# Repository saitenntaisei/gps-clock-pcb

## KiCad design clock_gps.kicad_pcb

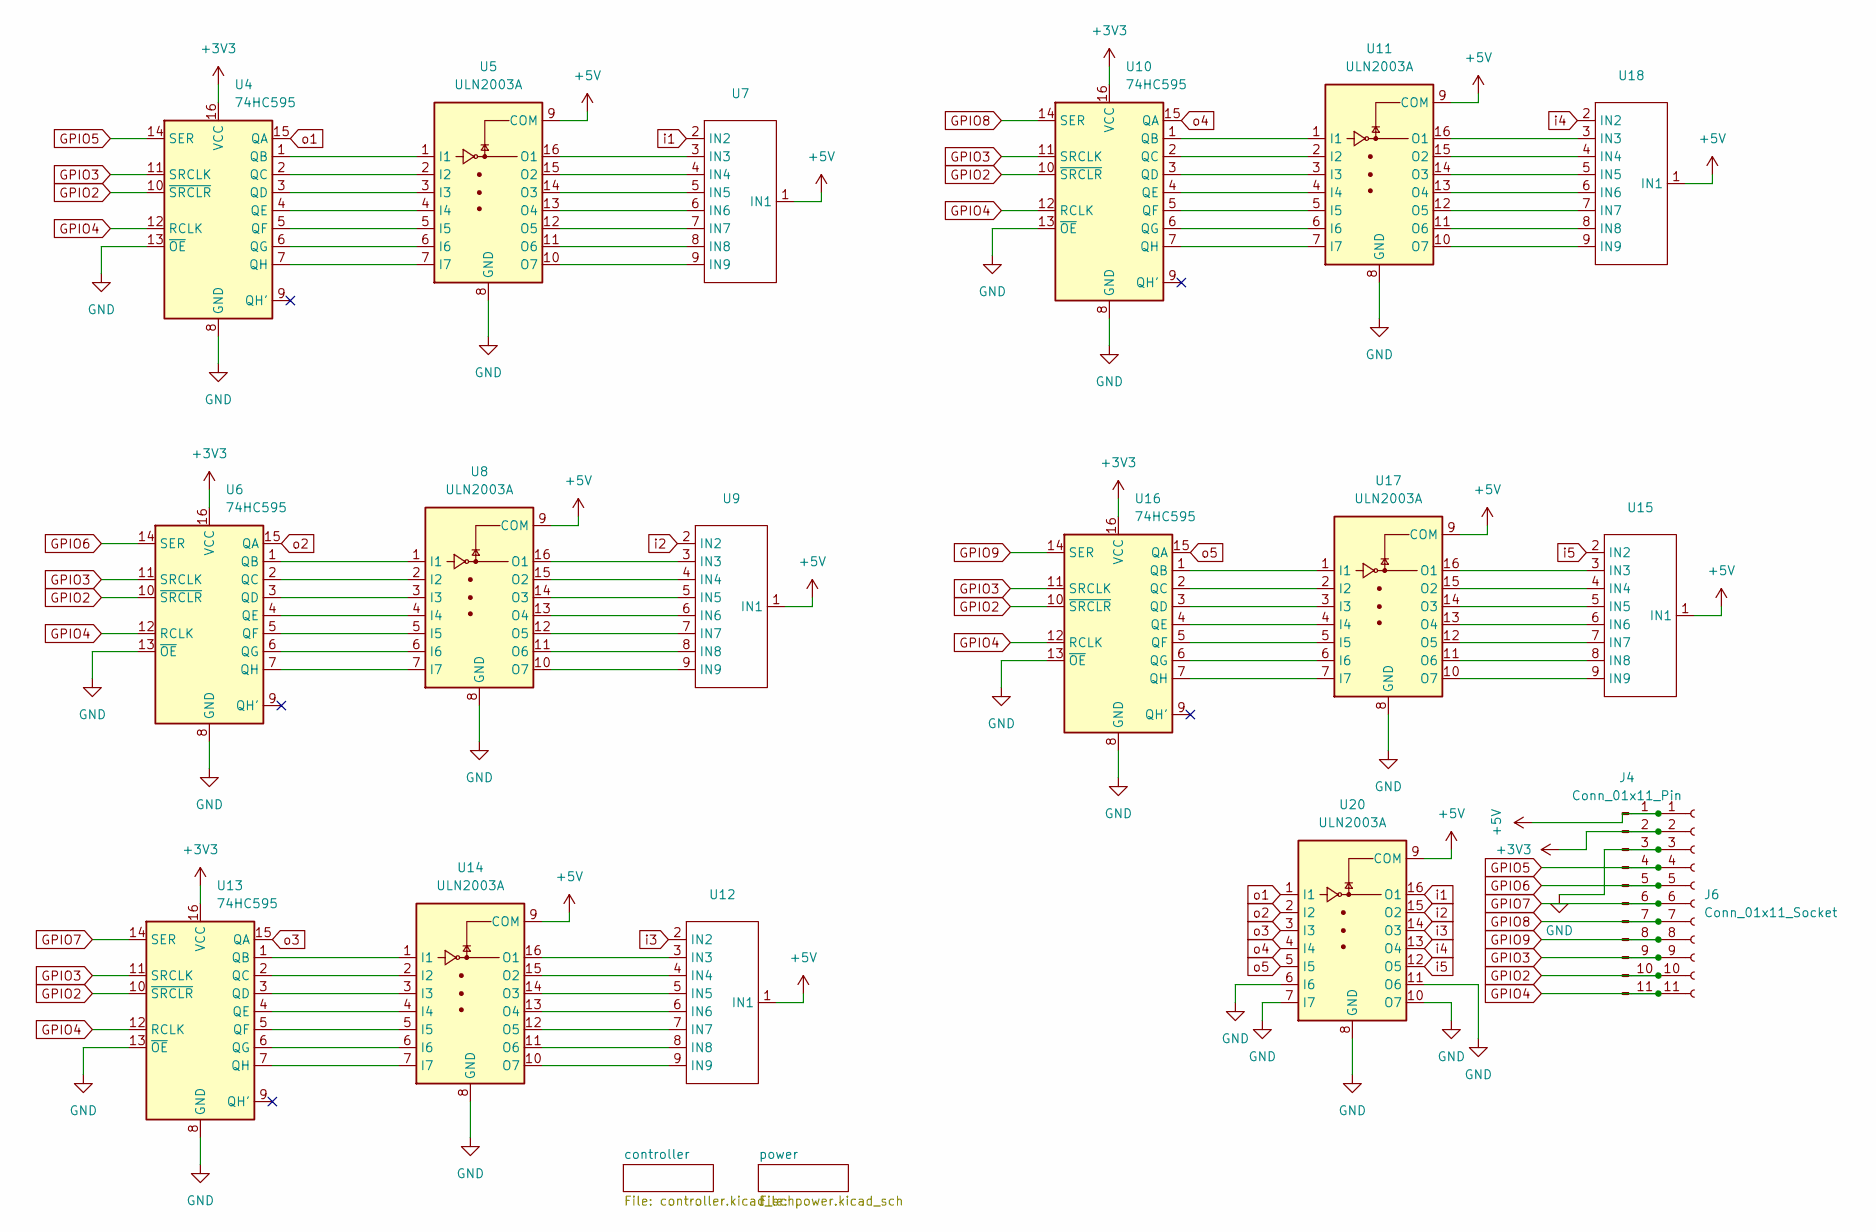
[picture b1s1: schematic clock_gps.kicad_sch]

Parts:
J4: Conn_01x11_Pin; PinHeader_1x11_P2.54mm_Vertical
J6: Conn_01x11_Socket; PinSocket_1x11_P2.54mm_Vertical
U4, U6, U10, U13, U16: 74HC595; SOIC-16_3.9x9.9mm_P1.27mm
U5, U8, U11, U14, U17, U20: ULN2003A; SOIC-16_3.9x9.9mm_P1.27mm
U7, U9, U12, U15, U18: NUM_IV-9

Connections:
+3V3: J4.2, J6.2, U4.16 (VCC), U6.16 (VCC), U10.16 (VCC), U13.16 (VCC), U16.16 (VCC); also elsewhere on the board
+5V: J4.1, J6.1, U5.9 (COM), U7.1 (IN1), U8.9 (COM), U9.1 (IN1), U11.9 (COM), U12.1 (IN1), U14.9 (COM), U15.1 (IN1), U17.9 (COM), U18.1 (IN1), U20.9 (COM); also elsewhere on the board
GND: J4.3, J6.3, U4.8 (GND), U4.13 (~OE), U5.8 (GND), U6.8 (GND), U6.13 (~OE), U8.8 (GND), U10.8 (GND), U10.13 (~OE), U11.8 (GND), U13.8 (GND), U13.13 (~OE), U14.8 (GND), U16.8 (GND), U16.13 (~OE), U17.8 (GND), U20.6 (I6), U20.7 (I7), U20.8 (GND), U20.10 (O7), U20.11 (O6); also elsewhere on the board
GPIO2: J4.10, J6.10, U4.10 (~SRCLR), U6.10 (~SRCLR), U10.10 (~SRCLR), U13.10 (~SRCLR), U16.10 (~SRCLR); also elsewhere on the board
GPIO3: J4.9, J6.9, U4.11 (SRCLK), U6.11 (SRCLK), U10.11 (SRCLK), U13.11 (SRCLK), U16.11 (SRCLK); also elsewhere on the board
GPIO4: J4.11, J6.11, U4.12 (RCLK), U6.12 (RCLK), U10.12 (RCLK), U13.12 (RCLK), U16.12 (RCLK); also elsewhere on the board
GPIO5: J4.4, J6.4, U4.14 (SER); also elsewhere on the board
GPIO6: J4.5, J6.5, U6.14 (SER); also elsewhere on the board
GPIO7: J4.6, J6.6, U13.14 (SER); also elsewhere on the board
GPIO8: J4.7, J6.7, U10.14 (SER); also elsewhere on the board
GPIO9: J4.8, J6.8, U16.14 (SER); also elsewhere on the board
unnamed: U4.1 (QB), U5.1 (I1)
unnamed: U4.2 (QC), U5.2 (I2)
unnamed: U4.3 (QD), U5.3 (I3)
unnamed: U4.4 (QE), U5.4 (I4)
unnamed: U4.5 (QF), U5.5 (I5)
unnamed: U4.6 (QG), U5.6 (I6)
unnamed: U4.7 (QH), U5.7 (I7)
unnamed: U5.16 (O1), U7.3 (IN3)
unnamed: U5.15 (O2), U7.4 (IN4)
unnamed: U5.14 (O3), U7.5 (IN5)
unnamed: U5.13 (O4), U7.6 (IN6)
unnamed: U5.12 (O5), U7.7 (IN7)
unnamed: U5.11 (O6), U7.8 (IN8)
unnamed: U5.10 (O7), U7.9 (IN9)
unnamed: U6.1 (QB), U8.1 (I1)
unnamed: U6.2 (QC), U8.2 (I2)
unnamed: U6.3 (QD), U8.3 (I3)
unnamed: U6.4 (QE), U8.4 (I4)
unnamed: U6.5 (QF), U8.5 (I5)
unnamed: U6.6 (QG), U8.6 (I6)
unnamed: U6.7 (QH), U8.7 (I7)
unnamed: U8.16 (O1), U9.3 (IN3)
unnamed: U8.15 (O2), U9.4 (IN4)
unnamed: U8.14 (O3), U9.5 (IN5)
unnamed: U8.13 (O4), U9.6 (IN6)
unnamed: U8.12 (O5), U9.7 (IN7)
unnamed: U8.11 (O6), U9.8 (IN8)
unnamed: U8.10 (O7), U9.9 (IN9)
unnamed: U10.1 (QB), U11.1 (I1)
unnamed: U10.2 (QC), U11.2 (I2)
unnamed: U10.3 (QD), U11.3 (I3)
unnamed: U10.4 (QE), U11.4 (I4)
unnamed: U10.5 (QF), U11.5 (I5)
unnamed: U10.6 (QG), U11.6 (I6)
unnamed: U10.7 (QH), U11.7 (I7)
unnamed: U11.16 (O1), U18.3 (IN3)
unnamed: U11.15 (O2), U18.4 (IN4)
unnamed: U11.14 (O3), U18.5 (IN5)
unnamed: U11.13 (O4), U18.6 (IN6)
unnamed: U11.12 (O5), U18.7 (IN7)
unnamed: U11.11 (O6), U18.8 (IN8)
unnamed: U11.10 (O7), U18.9 (IN9)
unnamed: U12.3 (IN3), U14.16 (O1)
unnamed: U12.4 (IN4), U14.15 (O2)
unnamed: U12.5 (IN5), U14.14 (O3)
unnamed: U12.6 (IN6), U14.13 (O4)
unnamed: U12.7 (IN7), U14.12 (O5)
unnamed: U12.8 (IN8), U14.11 (O6)
unnamed: U12.9 (IN9), U14.10 (O7)
unnamed: U13.1 (QB), U14.1 (I1)
unnamed: U13.2 (QC), U14.2 (I2)
unnamed: U13.3 (QD), U14.3 (I3)
unnamed: U13.4 (QE), U14.4 (I4)
unnamed: U13.5 (QF), U14.5 (I5)
unnamed: U13.6 (QG), U14.6 (I6)
unnamed: U13.7 (QH), U14.7 (I7)
unnamed: U15.3 (IN3), U17.16 (O1)
unnamed: U15.4 (IN4), U17.15 (O2)
unnamed: U15.5 (IN5), U17.14 (O3)
unnamed: U15.6 (IN6), U17.13 (O4)
unnamed: U15.7 (IN7), U17.12 (O5)
unnamed: U15.8 (IN8), U17.11 (O6)
unnamed: U15.9 (IN9), U17.10 (O7)
unnamed: U16.1 (QB), U17.1 (I1)
unnamed: U16.2 (QC), U17.2 (I2)
unnamed: U16.3 (QD), U17.3 (I3)
unnamed: U16.4 (QE), U17.4 (I4)
unnamed: U16.5 (QF), U17.5 (I5)
unnamed: U16.6 (QG), U17.6 (I6)
unnamed: U16.7 (QH), U17.7 (I7)
i1: U7.2 (IN2), U20.16 (O1)
i2: U9.2 (IN2), U20.15 (O2)
i3: U12.2 (IN2), U20.14 (O3)
i4: U18.2 (IN2), U20.13 (O4)
i5: U15.2 (IN2), U20.12 (O5)
o1: U4.15 (QA), U20.1 (I1)
o2: U6.15 (QA), U20.2 (I2)
o3: U13.15 (QA), U20.3 (I3)
o4: U10.15 (QA), U20.4 (I4)
o5: U16.15 (QA), U20.5 (I5)

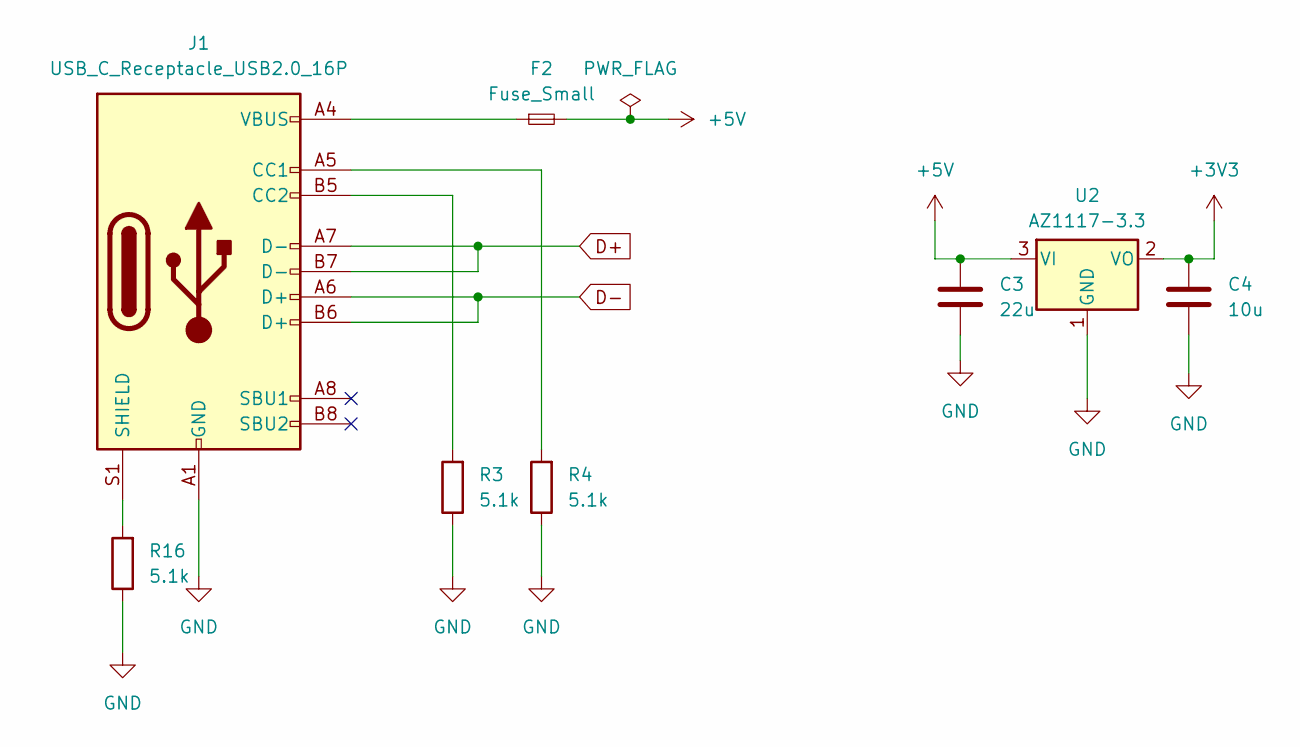
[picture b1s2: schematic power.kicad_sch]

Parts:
C3: 22u; C_0402_1005Metric
C4: 10u; C_0402_1005Metric
F2: Fuse_Small; Fuse_1210_3225Metric
J1: USB_C_Receptacle_USB2.0_16P; USB_C_Receptacle_G-Switch_GT-USB-7010ASV
R3, R4, R16: 5.1k; R_0402_1005Metric
U2: AZ1117-3.3; TO-252-2

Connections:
+3V3: C4.1, U2.2 (VO); also elsewhere on the board
+5V: C3.1, F2.2, U2.3 (VI); also elsewhere on the board
D+: J1.A7 (D-), J1.B7 (D-); also elsewhere on the board
D-: J1.A6 (D+), J1.B6 (D+); also elsewhere on the board
GND: C3.2, C4.2, J1.A1 (GND), J1.A12 (GND), J1.B1 (GND), J1.B12 (GND), R3.1, R4.1, R16.1, U2.1 (GND); also elsewhere on the board
unnamed: F2.1, J1.A4 (VBUS), J1.A9 (VBUS), J1.B4 (VBUS), J1.B9 (VBUS)
unnamed: J1.A5 (CC1), R4.2
unnamed: J1.B5 (CC2), R3.2
unnamed: J1.S1 (SHIELD), R16.2

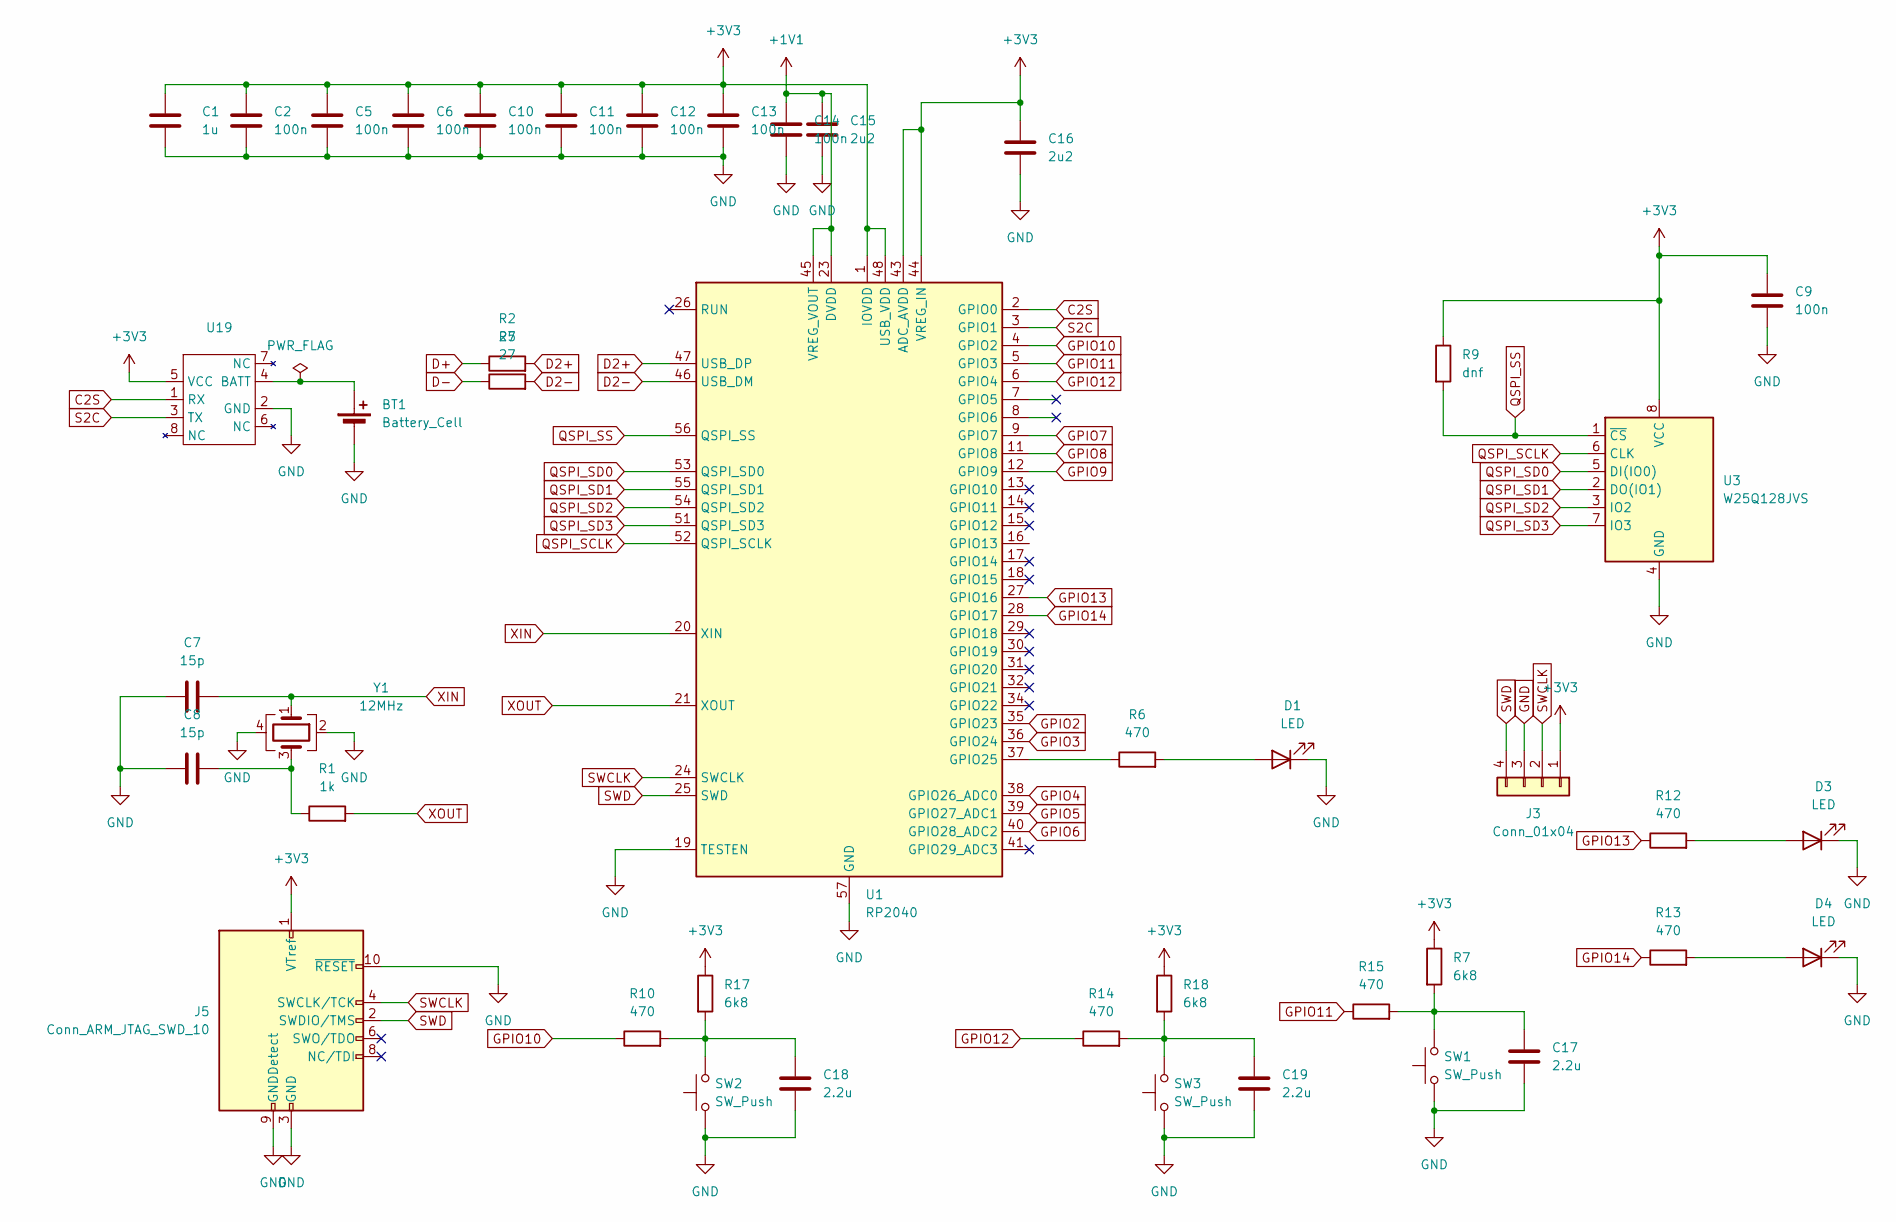
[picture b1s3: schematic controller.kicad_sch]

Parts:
BT1: Battery_Cell; BatteryHolder_Keystone_1060_1x2032
C1: 1u; C_0402_1005Metric
C2, C5, C6, C9, C10, C11, C12, C13, C14: 100n; C_0402_1005Metric
C7, C8: 15p; C_0402_1005Metric
C15, C16: 2u2; C_0402_1005Metric
C17, C18, C19: 2.2u; C_0402_1005Metric
D1, D3, D4: LED; LED_0603_1608Metric
J3: Conn_01x04; PinHeader_1x04_P2.54mm_Vertical
J5: Conn_ARM_JTAG_SWD_10; PinHeader_2x05_P1.27mm_Vertical
R1: 1k; R_0402_1005Metric
R2, R5: 27; R_0402_1005Metric
R6, R10, R12, R13, R14, R15: 470; R_0402_1005Metric
R7, R17, R18: 6k8; R_0402_1005Metric
R9: dnf; R_0402_1005Metric
SW1, SW2, SW3: SW_Push; SW_SPST_TL3342
U1: RP2040; QFN-56-1EP_7x7mm_P0.4mm_EP3.2x3.2mm
U3: W25Q128JVS; SOIC-8_5.23x5.23mm_P1.27mm
U19: PinHeader_2x04_P2.00mm_Vertical_SMD
Y1: 12MHz; Crystal_SMD_3225-4Pin_3.2x2.5mm

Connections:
+1V1: C14.2, C15.2, U1.23 (DVDD), U1.45 (VREG_VOUT), U1.50 (DVDD)
+3V3: C1.2, C2.2, C5.2, C6.2, C9.1, C10.2, C11.2, C12.2, C13.2, C16.1, J3.1, J5.1 (VTref), R7.1, R9.1, R17.1, R18.1, U1.1 (IOVDD), U1.10 (IOVDD), U1.22 (IOVDD), U1.33 (IOVDD), U1.42 (IOVDD), U1.43 (ADC_AVDD), U1.44 (VREG_IN), U1.48 (USB_VDD), U1.49 (IOVDD), U3.8 (VCC), U19.5 (VCC); also elsewhere on the board
C2S: U1.2 (GPIO0), U19.1 (RX)
D2+: R2.2, U1.47 (USB_DP)
D2-: R5.2, U1.46 (USB_DM)
D+: R2.1; also elsewhere on the board
D-: R5.1; also elsewhere on the board
GND: BT1.2 (-), C1.1, C2.1, C5.1, C6.1, C7.1, C8.1, C9.2, C10.1, C11.1, C12.1, C13.1, C14.1, C15.1, C16.2, C17.2, C18.2, C19.2, D1.1 (K), D3.1 (K), D4.1 (K), J3.3, J5.3 (GND), J5.5 (GND), J5.9 (GNDDetect), J5.10 (~RESET), SW1.1, SW2.1, SW3.1, U1.19 (TESTEN), U1.57 (GND), U3.4 (GND), U19.2 (GND), Y1.2, Y1.4; also elsewhere on the board
GPIO2: U1.35 (GPIO23); also elsewhere on the board
GPIO3: U1.36 (GPIO24); also elsewhere on the board
GPIO4: U1.38 (GPIO26_ADC0); also elsewhere on the board
GPIO5: U1.39 (GPIO27_ADC1); also elsewhere on the board
GPIO6: U1.40 (GPIO28_ADC2); also elsewhere on the board
GPIO7: U1.9 (GPIO7); also elsewhere on the board
GPIO8: U1.11 (GPIO8); also elsewhere on the board
GPIO9: U1.12 (GPIO9); also elsewhere on the board
GPIO10: R10.1, U1.4 (GPIO2)
GPIO11: R15.1, U1.5 (GPIO3)
GPIO12: R14.1, U1.6 (GPIO4)
GPIO13: R12.1, U1.27 (GPIO16)
GPIO14: R13.1, U1.28 (GPIO17)
unnamed: BT1.1 (+), U19.4 (BATT)
unnamed: C8.2, R1.1, Y1.3
unnamed: C17.1, R7.2, R15.2, SW1.2
unnamed: C18.1, R10.2, R17.2, SW2.2
unnamed: C19.1, R14.2, R18.2, SW3.2
unnamed: D1.2 (A), R6.2
unnamed: D3.2 (A), R12.2
unnamed: D4.2 (A), R13.2
unnamed: R6.1, U1.37 (GPIO25)
QSPI_SCLK: U1.52 (QSPI_SCLK), U3.6 (CLK)
QSPI_SD0: U1.53 (QSPI_SD0), U3.5 (DI(IO0))
QSPI_SD1: U1.55 (QSPI_SD1), U3.2 (DO(IO1))
QSPI_SD2: U1.54 (QSPI_SD2), U3.3 (IO2)
QSPI_SD3: U1.51 (QSPI_SD3), U3.7 (IO3)
QSPI_SS: R9.2, U1.56 (QSPI_SS), U3.1 (~CS)
S2C: U1.3 (GPIO1), U19.3 (TX)
SWCLK: J3.2, J5.4 (SWCLK/TCK), U1.24 (SWCLK)
SWD: J3.4, J5.2 (SWDIO/TMS), U1.25 (SWD)
XIN: C7.2, U1.20 (XIN), Y1.1
XOUT: R1.2, U1.21 (XOUT)

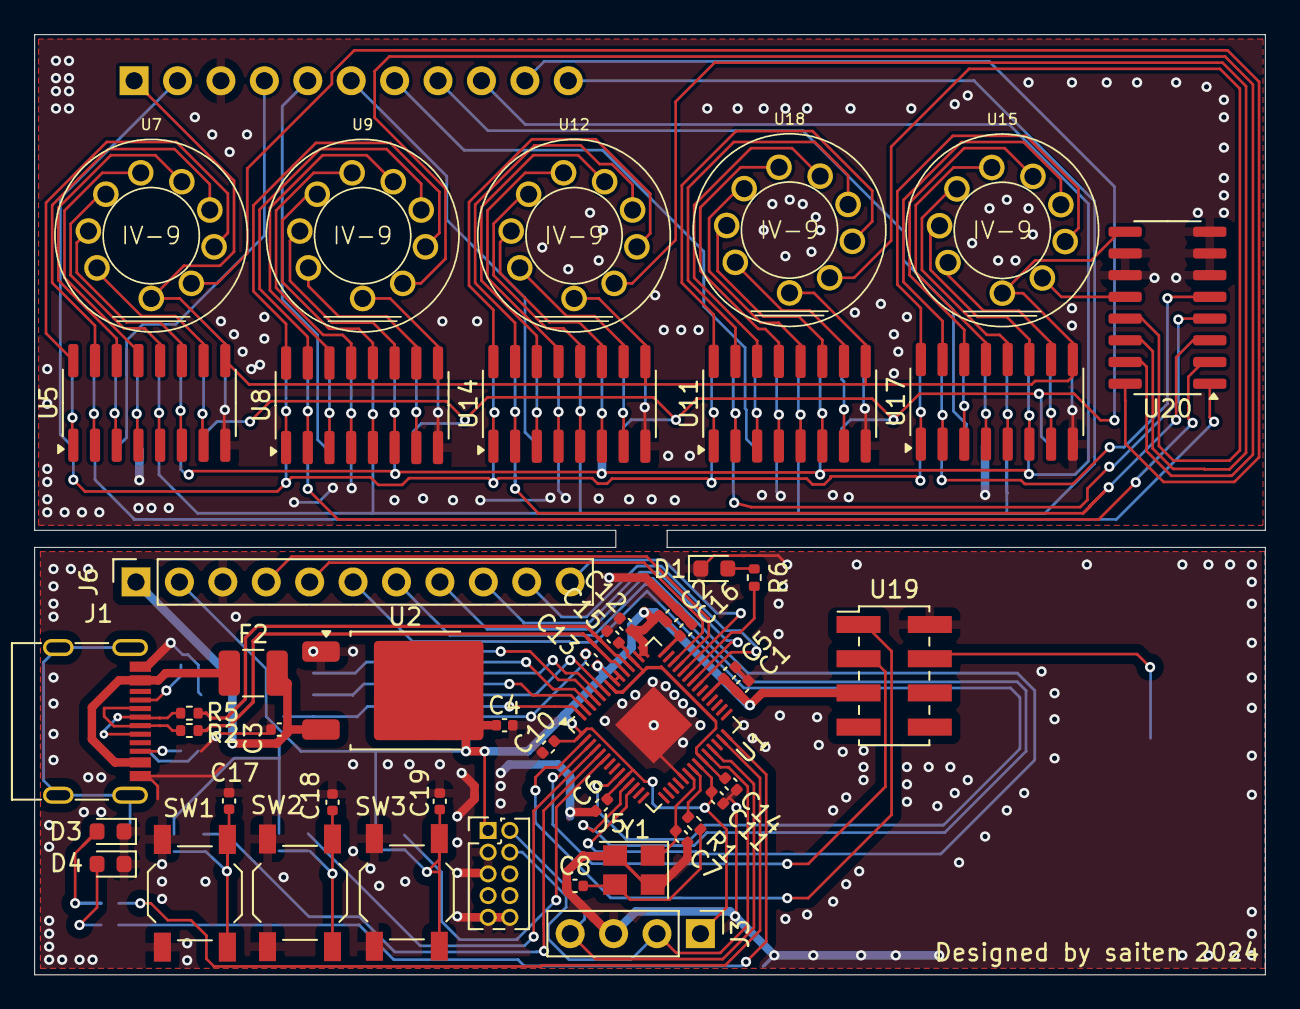
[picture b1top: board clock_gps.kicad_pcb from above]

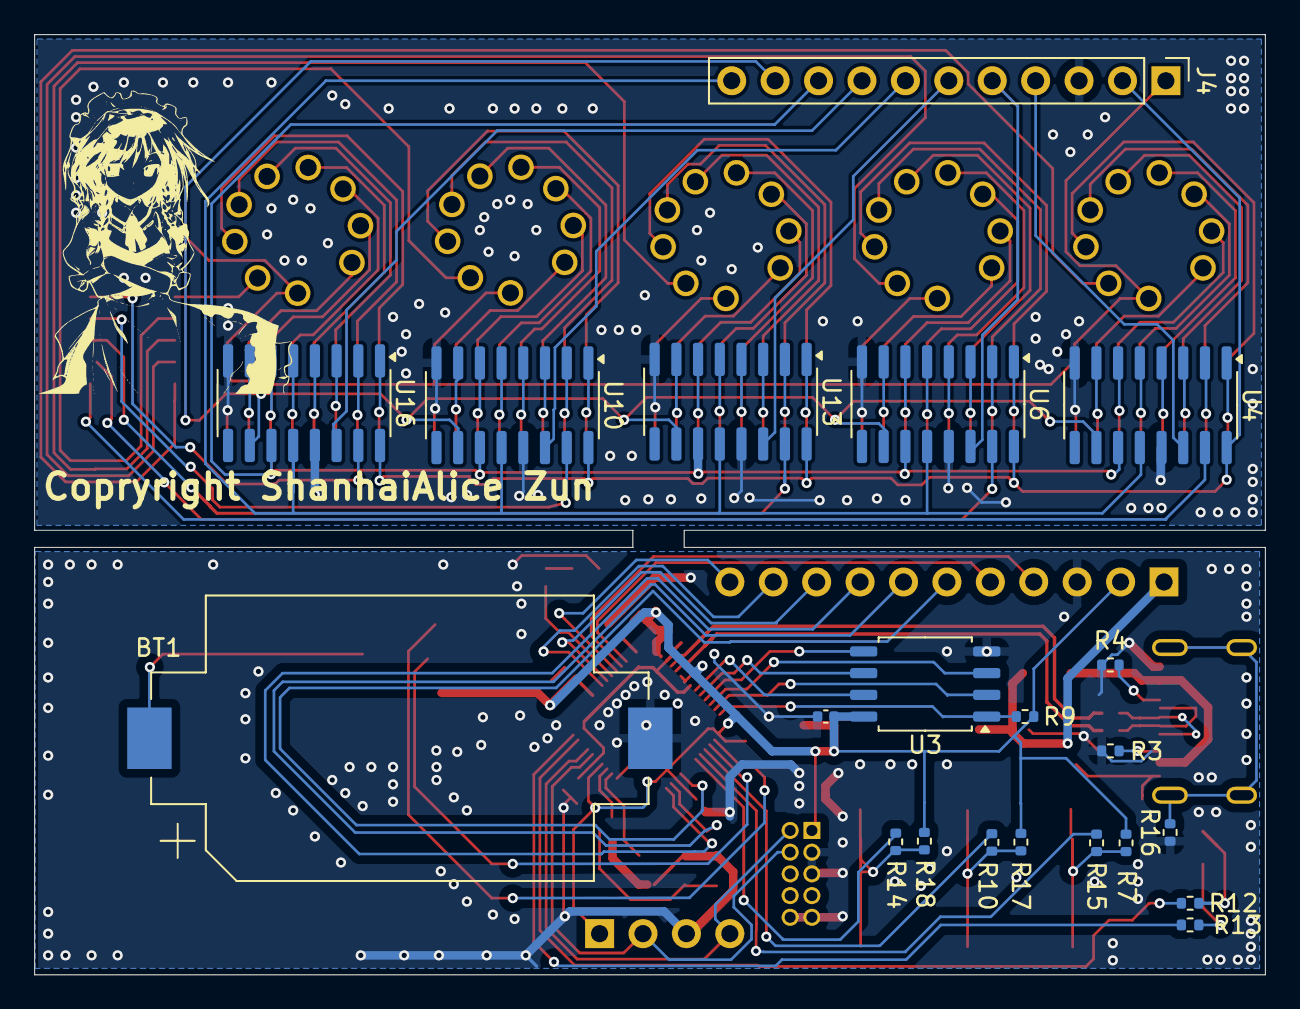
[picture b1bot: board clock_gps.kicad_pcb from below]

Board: 2 copper layers, 72.0 x 55.0 mm, 70 parts (22 on the bottom side), 126 nets.

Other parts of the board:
Copryright ShanhaiAlice Zun: LOGO; sakuya

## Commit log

2024-12-31 feat: add pcb
